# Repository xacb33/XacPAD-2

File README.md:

# XacPAD-2

The second attemp of my previously failed XacPAD, a general use/gaming macropad.

Changes from v1:
Altough the main issue with v1 was the building process, not the design (my soldering iron was too weak) I have made a couple of small changes to improve the general design and the firmware, but keeping the essencve the same:
- Wired switches in a matrix, instead of direct pin
- Added a rotary encoder using the free pins from wiring the keys as a matrix
- Simplified the firmware. (It probably won't work, but will fix it when I have the real hardware to try)

Specifications
BOM:

8x Cherry MX Switches

5x SK6812 MINI Leds

1x XIAO RP2040

8x Blank DSA Keycaps

4x M3x16 Bolt

4x M3 Heatset

1x 0.91' I2C OLED Display

1x EC11 Rotary encoder

8x through-hole 1N4148 Diodes

Others:

QMK Firmware (In xacpad2 folder)
XacPad v2 case BASE.stl
XacPad v2 case TOP.stl

Huge thanks to HackClub for doing this project https://stardance.hackclub.com/

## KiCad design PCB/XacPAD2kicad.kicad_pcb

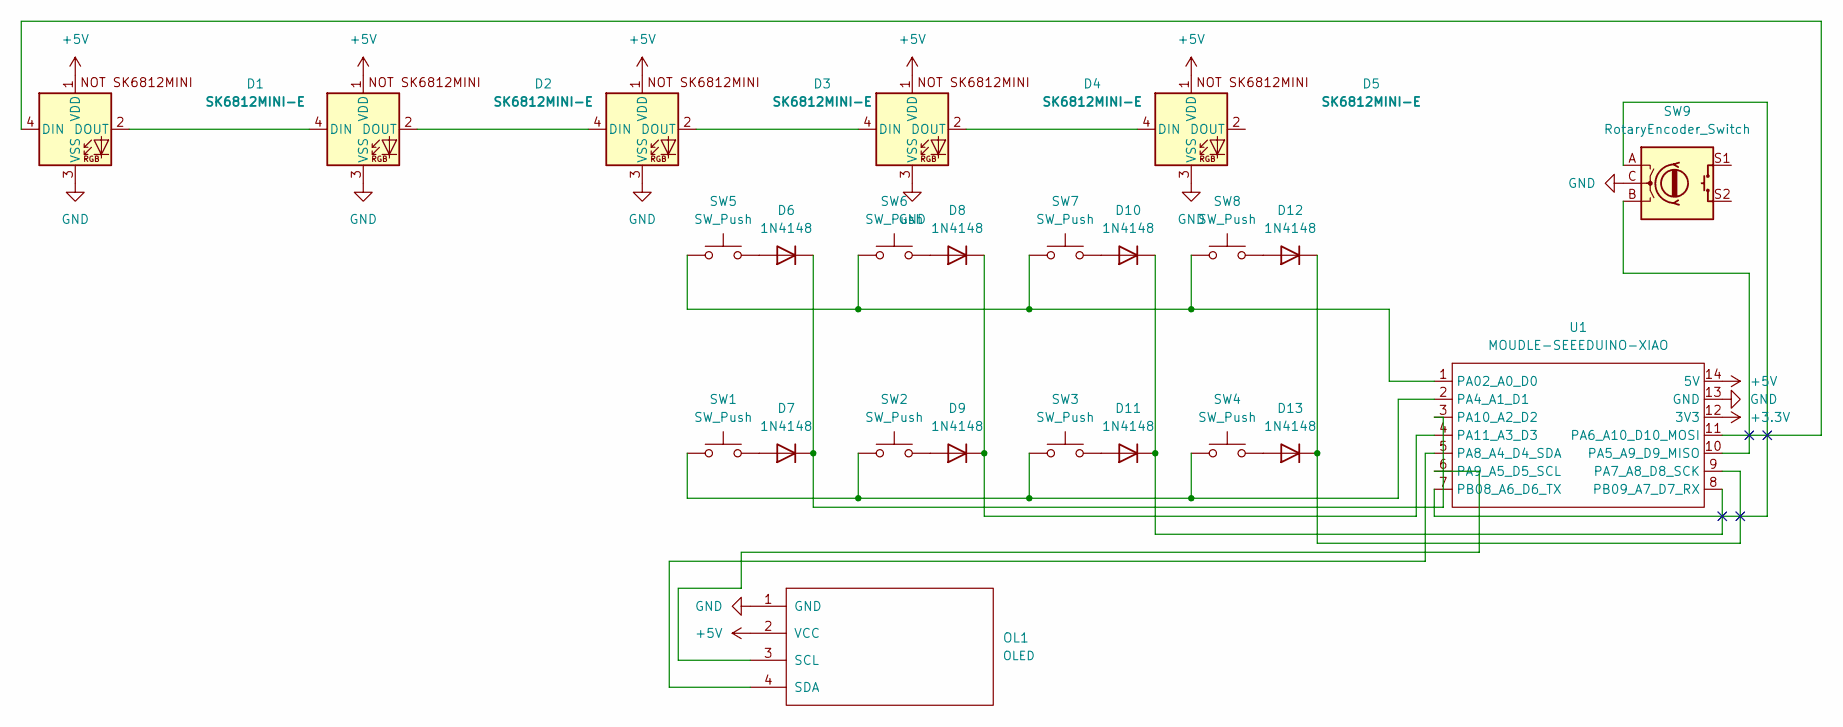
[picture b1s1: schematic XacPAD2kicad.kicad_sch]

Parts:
D1, D2, D3, D4, D5: SK6812MINI-E; SK6812MINI-E_fixed
D6, D7, D8, D9, D10, D11, D12, D13: 1N4148; D_DO-35_SOD27_P7.62mm_Horizontal
OL1: OLED; SSD1306-0.91-OLED-4pin-128x32
SW1, SW2, SW3, SW4, SW5, SW6, SW7, SW8: SW_Push; MX-Solderable-1U
SW9: RotaryEncoder_Switch; RotaryEncoder_Alps_EC11E-Switch_Vertical_H20mm
U1: MOUDLE-SEEEDUINO-XIAO; XIAO-Generic-Hybrid-14P-2.54-21X17.8MM

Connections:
+3.3V: U1.12 (3V3)
+5V: D1.1 (VDD), D2.1 (VDD), D3.1 (VDD), D4.1 (VDD), D5.1 (VDD), OL1.2 (VCC), U1.14 (5V)
GND: D1.3 (VSS), D2.3 (VSS), D3.3 (VSS), D4.3 (VSS), D5.3 (VSS), OL1.1 (GND), SW9.C, U1.13 (GND)
unnamed: D1.4 (DIN), U1.11 (PA6_A10_D10_MOSI)
unnamed: D1.2 (DOUT), D2.4 (DIN)
unnamed: D2.2 (DOUT), D3.4 (DIN)
unnamed: D3.2 (DOUT), D4.4 (DIN)
unnamed: D4.2 (DOUT), D5.4 (DIN)
unnamed: D6.2 (A), SW5.2
unnamed: D6.1 (K), D7.1 (K), U1.3 (PA10_A2_D2)
unnamed: D7.2 (A), SW1.2
unnamed: D8.2 (A), SW6.2
unnamed: D8.1 (K), D9.1 (K), U1.4 (PA11_A3_D3)
unnamed: D9.2 (A), SW2.2
unnamed: D10.2 (A), SW7.2
unnamed: D10.1 (K), D11.1 (K), U1.8 (PB09_A7_D7_RX)
unnamed: D11.2 (A), SW3.2
unnamed: D12.2 (A), SW8.2
unnamed: D12.1 (K), D13.1 (K), U1.9 (PA7_A8_D8_SCK)
unnamed: D13.2 (A), SW4.2
unnamed: OL1.3 (SCL), U1.6 (PA9_A5_D5_SCL)
unnamed: OL1.4 (SDA), U1.5 (PA8_A4_D4_SDA)
unnamed: SW5.1, SW6.1, SW7.1, SW8.1, U1.1 (PA02_A0_D0)
unnamed: SW1.1, SW2.1, SW3.1, SW4.1, U1.2 (PA4_A1_D1)
unnamed: SW9.B, U1.10 (PA5_A9_D9_MISO)
unnamed: SW9.A, U1.7 (PB08_A6_D6_TX)

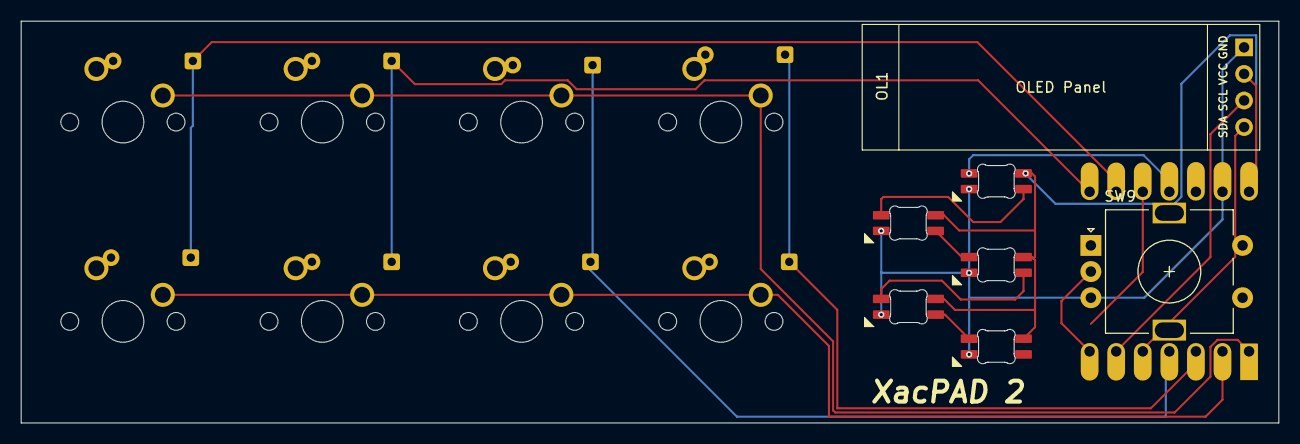
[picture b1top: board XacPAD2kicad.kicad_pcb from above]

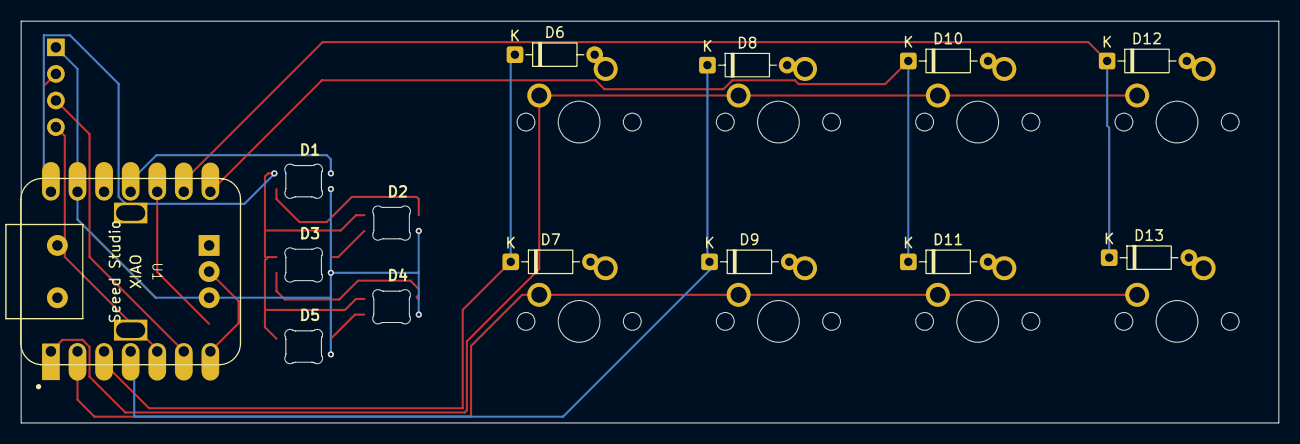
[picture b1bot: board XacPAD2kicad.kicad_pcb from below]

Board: 2 copper layers, 120.2 x 38.4 mm, 24 parts (22 on the bottom side), 25 nets.
